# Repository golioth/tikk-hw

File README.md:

# Tikk Bluetooth Sensor / Output Board

We created the Tikk board as an affordable* board ($15 in low volume) for displaying the capabilities of Golioth's Bluetooth Connectivity. It plugs into a low cost ($3) Tenstar Robot nRF52840 breakout board, targeted at Keybord makers. We will have many of these nodes surrounding a Golioth gateway to showcase all of the uplink and downlink functions available to users. The focus was on easily demonstrated functions, such as LEDs and motor drivings for outputs and various in-tree Zephyr supported sensors for inputs.

## Rev A Preview Image

## Rev A Photos

## Features

This board has the following characteristics when soldered to something like the Tenstar Promicro

* 105 LEDs in 0402 format, individually addressable in a 7x15 matrix with the IS31FL3731
* Two H-Bridge chips (L9110S) for driving a single stepper or two dc motors
* 3 axis accelerometer (LIS2DH12)
* Temperature sensor (TMP102)
* QWIIC / Stemma header to expand breakout boards*
* User button
* Reset button
* A voltage divider that monitors battery voltage

Additional capabilities added by the Tenstar ProMicro and nRF52840

* Additional GPIOs I can solder to (5 digital, one analog)
* LiPo battery charger on board
* Load switch for all peripherals except motor driver
* USB Input to the nRF52840 (get serial terminal using USB-CDC)
* NFC tag emulation (via the nRF52840 and onboard flex connector)

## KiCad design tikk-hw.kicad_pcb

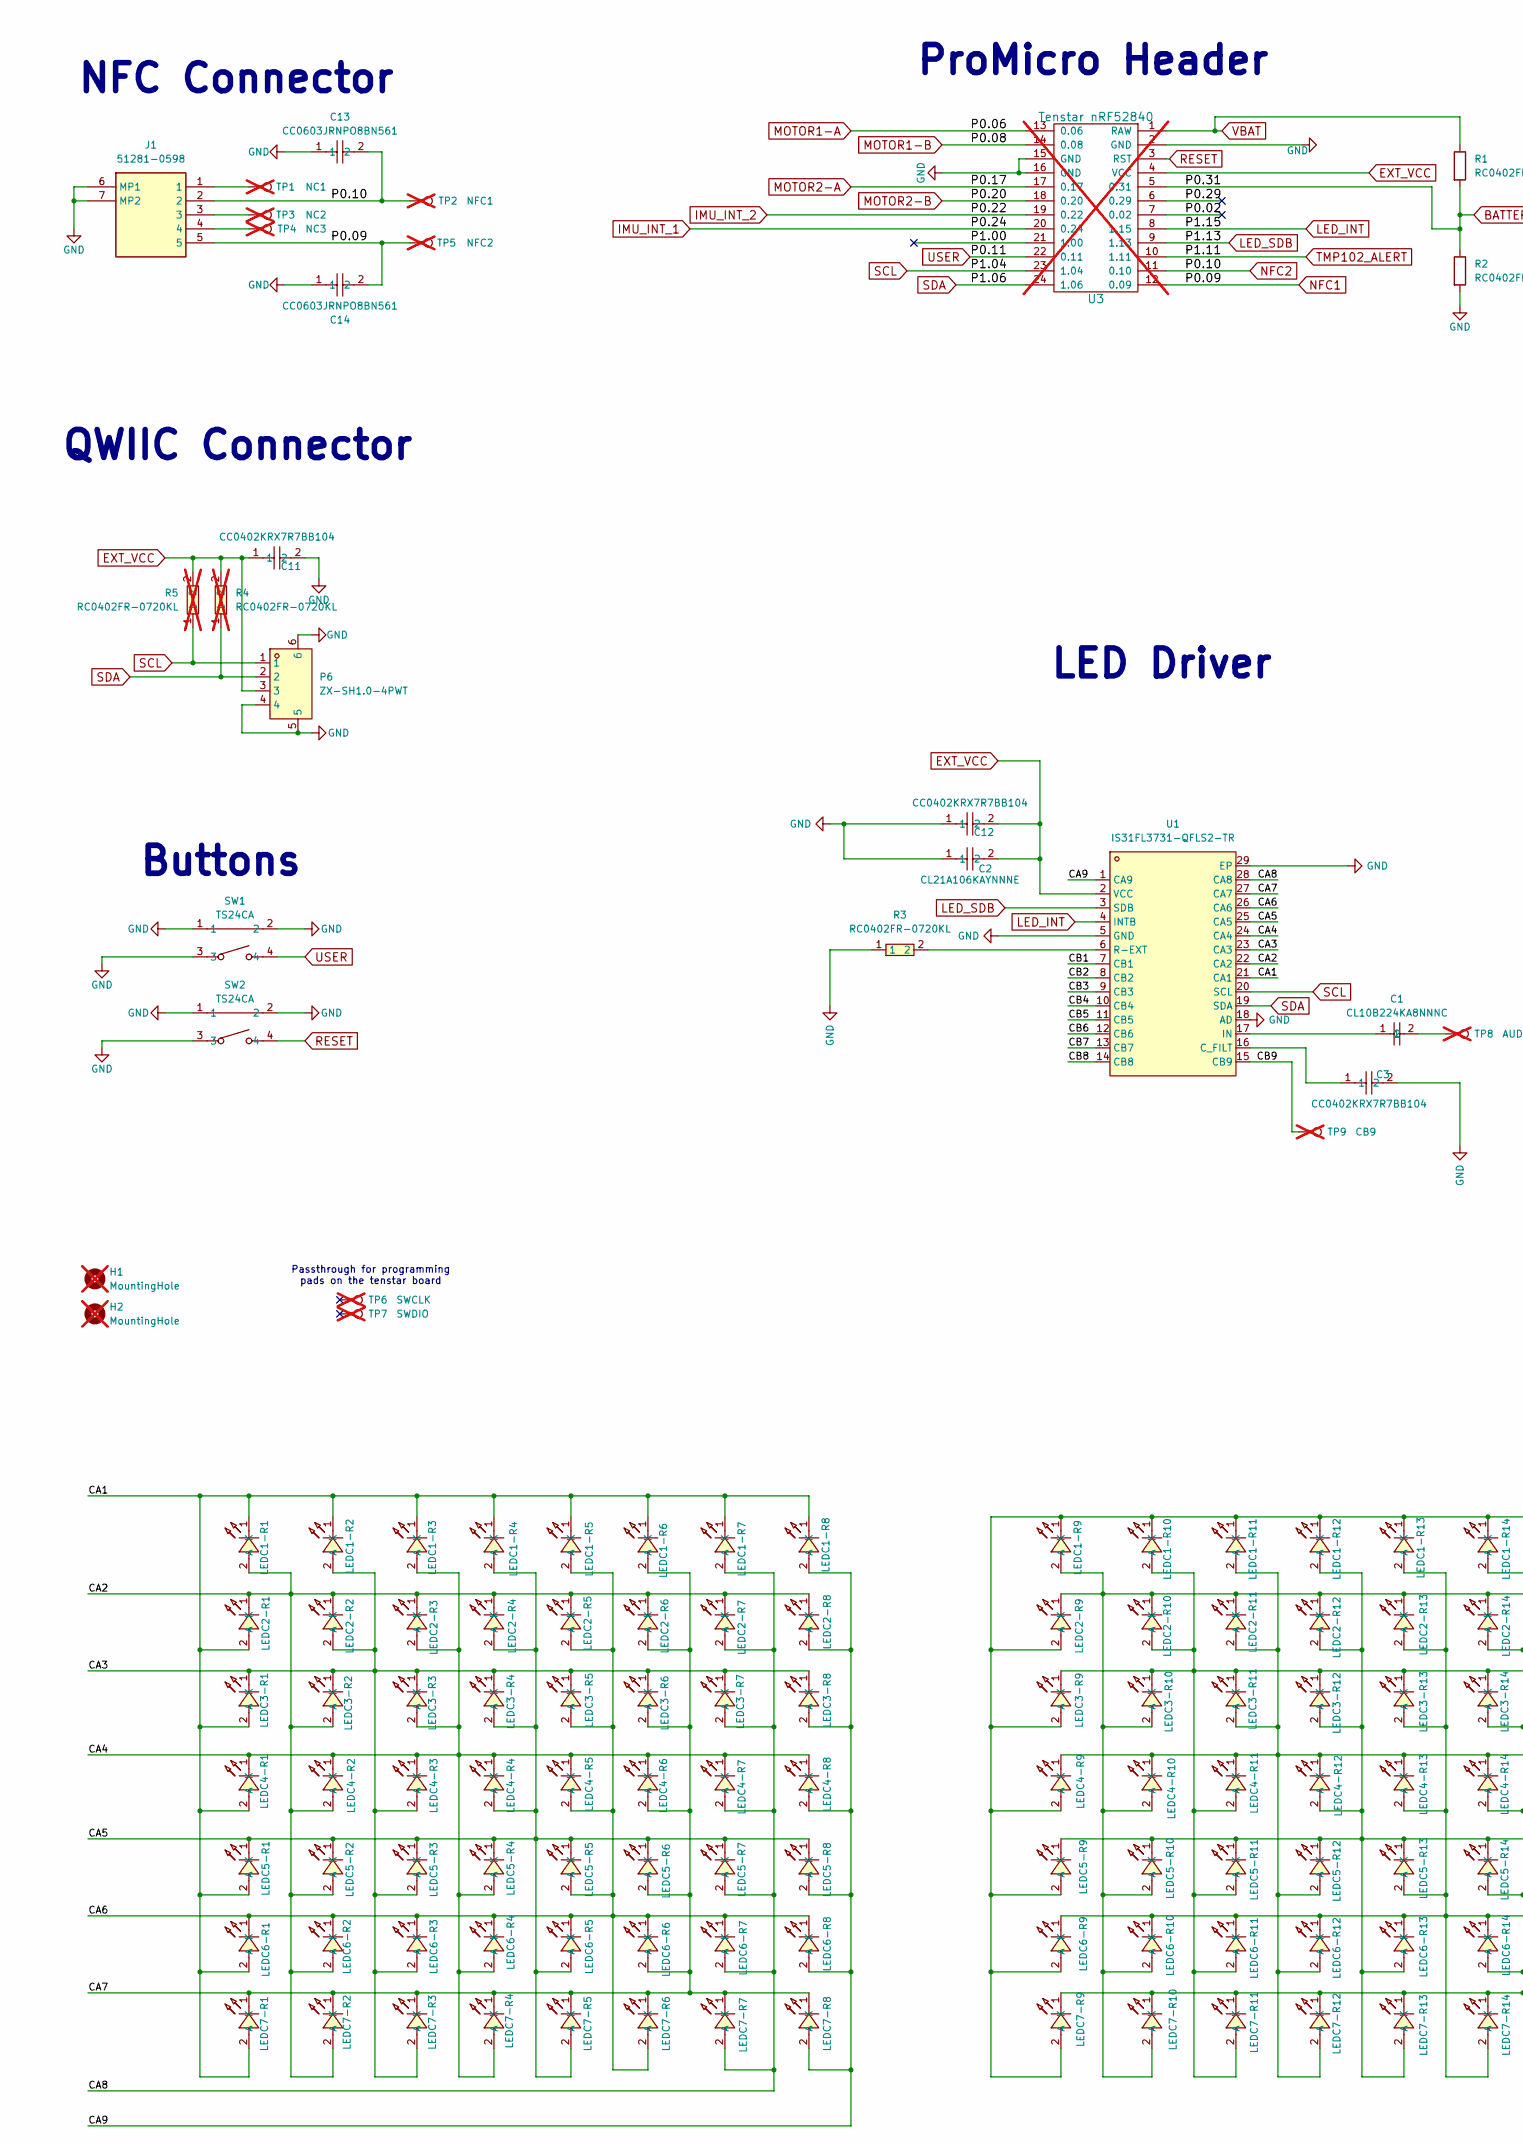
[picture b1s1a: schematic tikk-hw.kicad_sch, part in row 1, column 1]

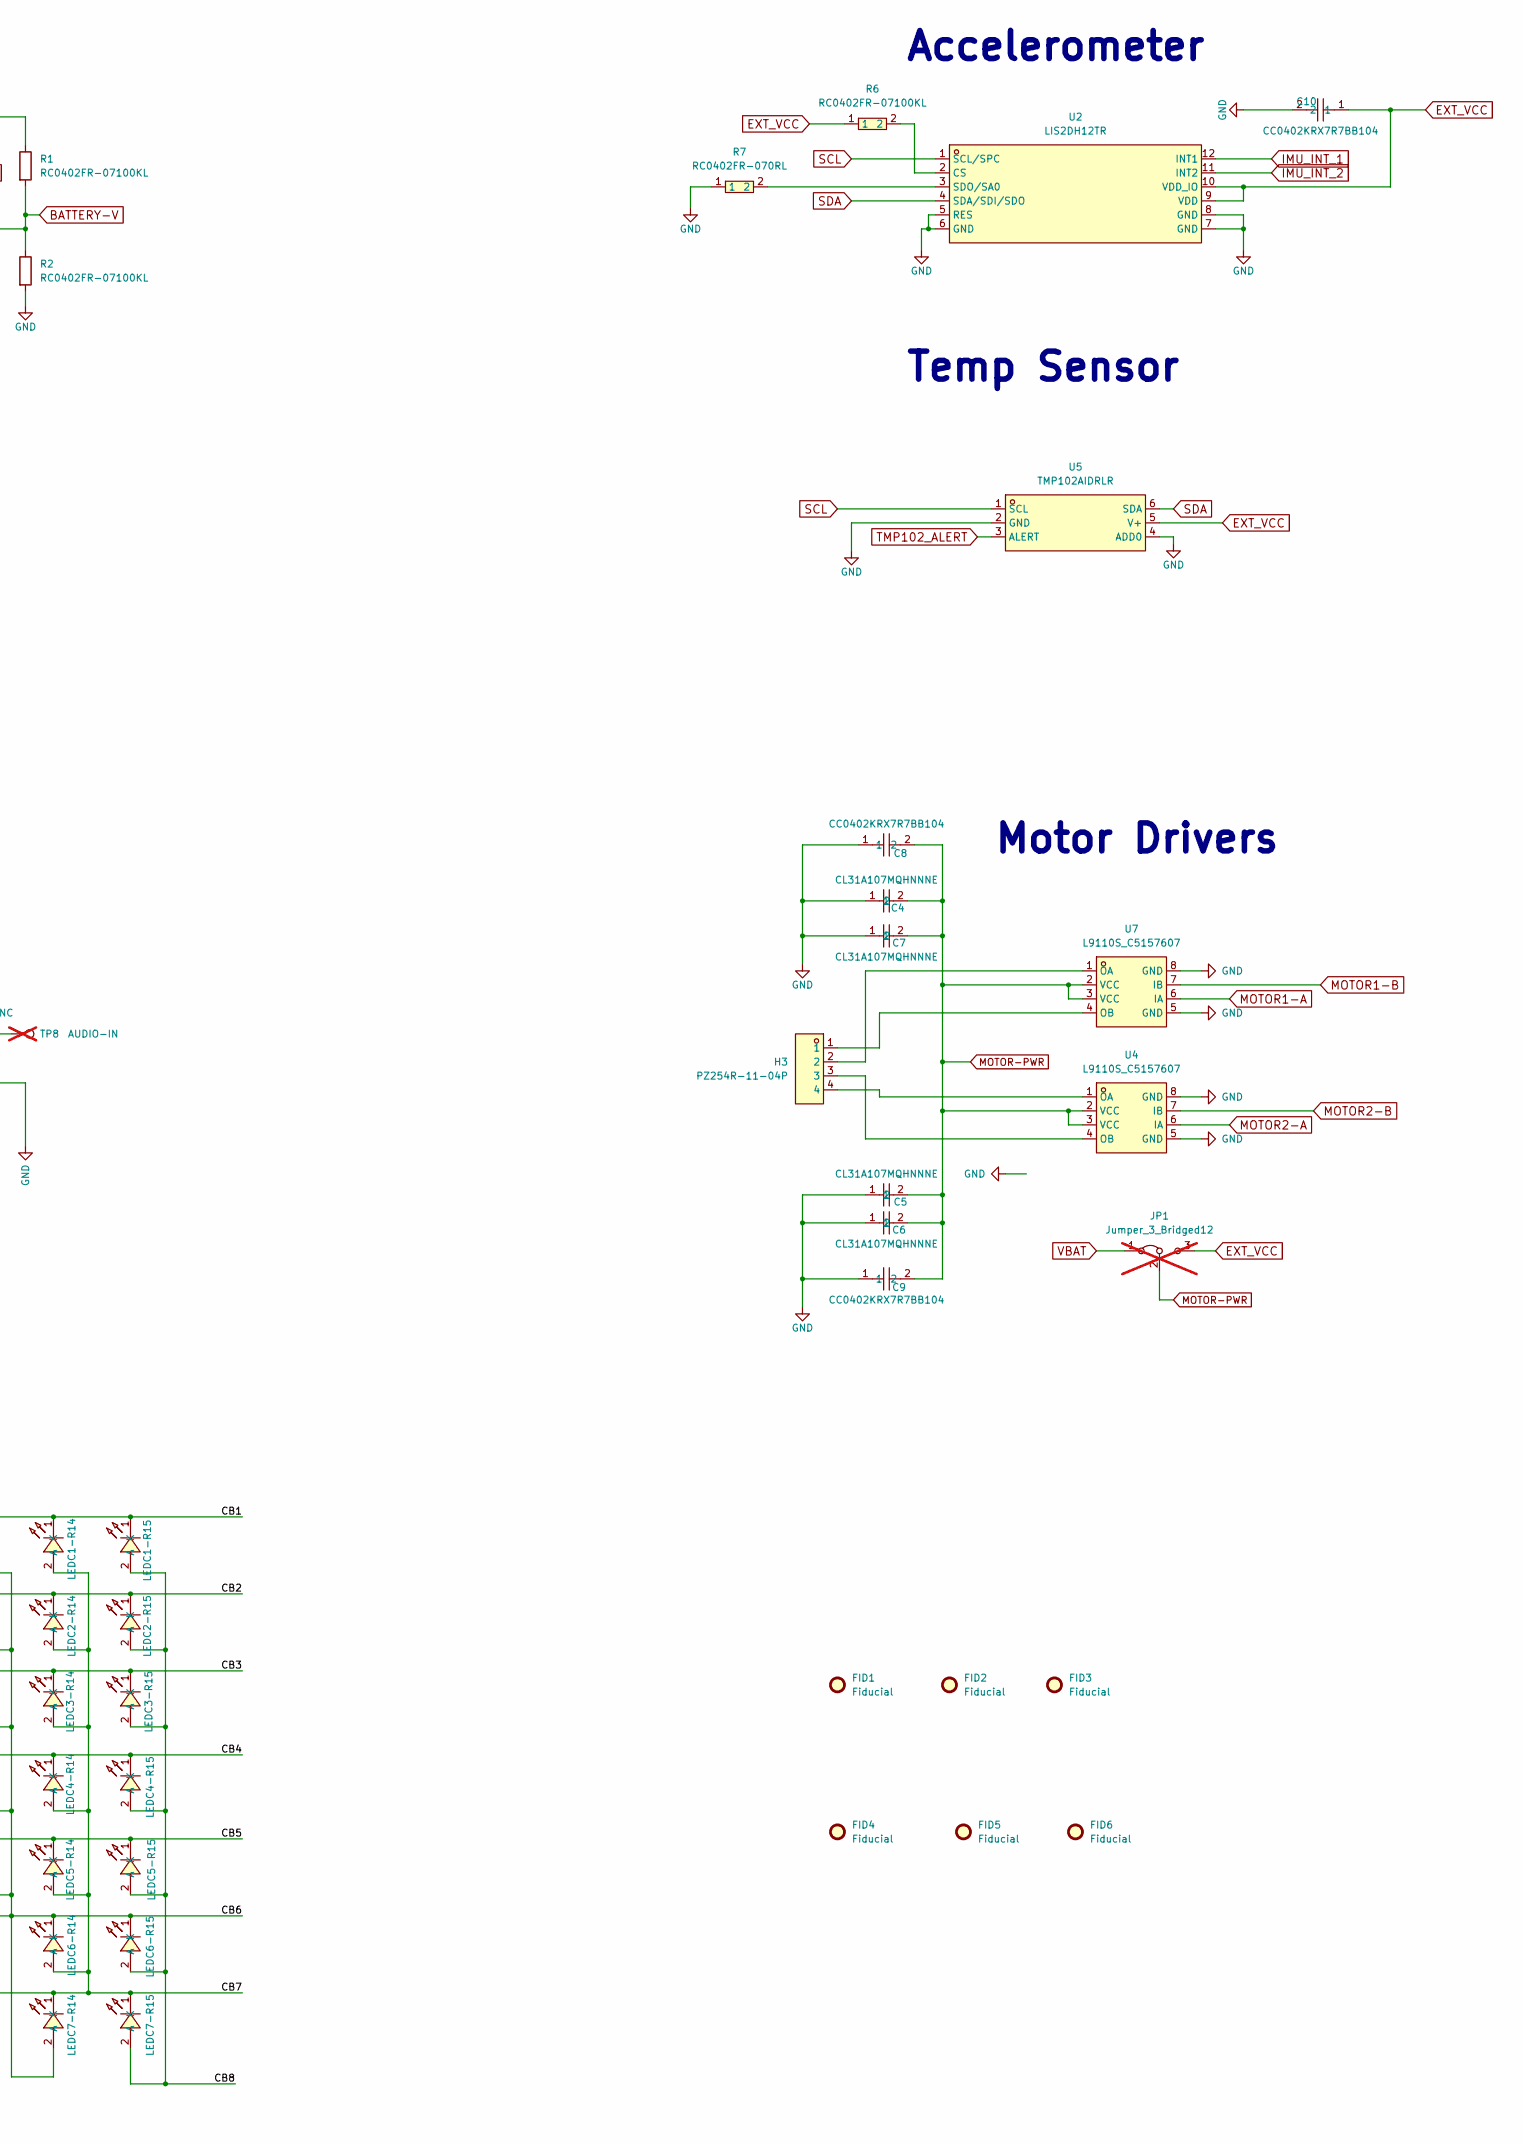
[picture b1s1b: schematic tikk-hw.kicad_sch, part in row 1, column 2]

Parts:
C1: CL10B224KA8NNNC; C0603; LCSC Part C21120
C2: CL21A106KAYNNNE; C0805; LCSC Part C15850
C3, C8, C9, C10, C11, C12: CC0402KRX7R7BB104; C0402; LCSC Part C60474
C4, C5, C6, C7: CL31A107MQHNNNE; C1206; LCSC Part C15008
C13, C14: CC0603JRNPO8BN561; C0603; LCSC Part C519396
FID1, FID2, FID3, FID4, FID5, FID6: Fiducial; Fiducial_0.5mm_Mask1mm
H1, H2: MountingHole; MountingHole_2.1mm; not fitted
H3: PZ254R-11-04P; HDR-TH_4P-P2.54-H-M-W10.4; LCSC Part C492412
J1: 51281-0598; 512810598; Mouser Part Number 538-51281-0598
JP1: Jumper_3_Bridged12; SolderJumper-3_P1.3mm_Bridged12_Pad1.0x1.5mm_NumberLabels; not fitted
LEDC1-R1, LEDC1-R2, LEDC1-R3, LEDC1-R4, LEDC1-R5, LEDC1-R6, LEDC1-R7, LEDC1-R8, LEDC1-R9, LEDC1-R10, LEDC1-R11, LEDC1-R12, LEDC1-R13, LEDC1-R14, LEDC1-R15, LEDC2-R1, LEDC2-R2, LEDC2-R3, LEDC2-R4, LEDC2-R5, LEDC2-R6, LEDC2-R7, LEDC2-R8, LEDC2-R9, LEDC2-R10, LEDC2-R11, LEDC2-R12, LEDC2-R13, LEDC2-R14, LEDC2-R15, LEDC3-R1, LEDC3-R2, LEDC3-R3, LEDC3-R4, LEDC3-R5, LEDC3-R6, LEDC3-R7, LEDC3-R8, LEDC3-R9, LEDC3-R10, LEDC3-R11, LEDC3-R12, LEDC3-R13, LEDC3-R14, LEDC3-R15, LEDC4-R1, LEDC4-R2, LEDC4-R3, LEDC4-R4, LEDC4-R5, LEDC4-R6, LEDC4-R7, LEDC4-R8, LEDC4-R9, LEDC4-R10, LEDC4-R11, LEDC4-R12, LEDC4-R13, LEDC4-R14, LEDC4-R15, LEDC5-R1, LEDC5-R2, LEDC5-R3, LEDC5-R4, LEDC5-R5, LEDC5-R6, LEDC5-R7, LEDC5-R8, LEDC5-R9, LEDC5-R10, LEDC5-R11, LEDC5-R12, LEDC5-R13, LEDC5-R14, LEDC5-R15, LEDC6-R1, LEDC6-R2, LEDC6-R3, LEDC6-R4, LEDC6-R5, LEDC6-R6, LEDC6-R7, LEDC6-R8, LEDC6-R9, LEDC6-R10, LEDC6-R11, LEDC6-R12, LEDC6-R13, LEDC6-R14, LEDC6-R15, LEDC7-R1, LEDC7-R2, LEDC7-R3, LEDC7-R4, LEDC7-R5, LEDC7-R6, LEDC7-R7, LEDC7-R8, LEDC7-R9, LEDC7-R10, LEDC7-R11, LEDC7-R12, LEDC7-R13, LEDC7-R14, LEDC7-R15: F.0402.00003/P2-0402R1TS2-045T-001; LED0402-RD; LCSC Part C7496803
P6: ZX-SH1.0-4PWT; CONN-SMD_4P-P1.00_MEGASTAR_ZX-SH1.0-4PWT; LCSC Part C7430446
R1, R2: RC0402FR-07100KL; R_0402_1005Metric
R3: RC0402FR-0720KL; R0402; LCSC Part C93942
R4, R5: RC0402FR-0720KL; R0402; LCSC Part C93942; not fitted
R6: RC0402FR-07100KL; R0402; LCSC Part C60491
R7: RC0402FR-070RL; R0402; LCSC Part C106231
SW1, SW2: TS24CA; SW-SMD_TS24CA; LCSC Part C393942
TP1: NC1; TestPoint_Pad_1.0x1.0mm; not fitted
TP2: NFC1; TestPoint_Pad_1.0x1.0mm; not fitted
TP3: NC2; TestPoint_Pad_1.0x1.0mm; not fitted
TP4: NC3; TestPoint_Pad_1.0x1.0mm; not fitted
TP5: NFC2; TestPoint_Pad_1.0x1.0mm; not fitted
TP6: SWCLK; TestPoint_THTPad_1.0x1.0mm_Drill0.5mm; not fitted
TP7: SWDIO; TestPoint_THTPad_1.0x1.0mm_Drill0.5mm; not fitted
TP8: AUDIO-IN; TestPoint_Pad_D1.0mm; not fitted
TP9: CB9; TestPoint_Pad_D1.0mm; not fitted
U1: IS31FL3731-QFLS2-TR; QFN-28_L4.0-W4.0-P0.40-BL-EP; LCSC Part C191206
U2: LIS2DH12TR; LGA-12_L2.0-W2.0-P0.50-BL; LCSC Part C110926
U3: Tenstar nRF52840; tenstar_nrf52840; not fitted
U4, U7: L9110S_C5157607; SOP-8_L4.9-W3.9-P1.27-LS6.0-BL; LCSC Part C5157607
U5: TMP102AIDRLR; SOT-563_L1.6-W1.2-P0.50-LS1.6-BR; LCSC Part C99269

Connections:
/CA1: LEDC1-R1.1 (K), LEDC1-R2.1 (K), LEDC1-R3.1 (K), LEDC1-R4.1 (K), LEDC1-R5.1 (K), LEDC1-R6.1 (K), LEDC1-R7.1 (K), LEDC1-R8.1 (K), LEDC2-R1.2 (A), LEDC3-R1.2 (A), LEDC4-R1.2 (A), LEDC5-R1.2 (A), LEDC6-R1.2 (A), LEDC7-R1.2 (A), U1.21 (CA1)
/CA2: LEDC1-R1.2 (A), LEDC2-R1.1 (K), LEDC2-R2.1 (K), LEDC2-R3.1 (K), LEDC2-R4.1 (K), LEDC2-R5.1 (K), LEDC2-R6.1 (K), LEDC2-R7.1 (K), LEDC2-R8.1 (K), LEDC3-R2.2 (A), LEDC4-R2.2 (A), LEDC5-R2.2 (A), LEDC6-R2.2 (A), LEDC7-R2.2 (A), U1.22 (CA2)
/CA3: LEDC1-R2.2 (A), LEDC2-R2.2 (A), LEDC3-R1.1 (K), LEDC3-R2.1 (K), LEDC3-R3.1 (K), LEDC3-R4.1 (K), LEDC3-R5.1 (K), LEDC3-R6.1 (K), LEDC3-R7.1 (K), LEDC3-R8.1 (K), LEDC4-R3.2 (A), LEDC5-R3.2 (A), LEDC6-R3.2 (A), LEDC7-R3.2 (A), U1.23 (CA3)
/CA4: LEDC1-R3.2 (A), LEDC2-R3.2 (A), LEDC3-R3.2 (A), LEDC4-R1.1 (K), LEDC4-R2.1 (K), LEDC4-R3.1 (K), LEDC4-R4.1 (K), LEDC4-R5.1 (K), LEDC4-R6.1 (K), LEDC4-R7.1 (K), LEDC4-R8.1 (K), LEDC5-R4.2 (A), LEDC6-R4.2 (A), LEDC7-R4.2 (A), U1.24 (CA4)
/CA5: LEDC1-R4.2 (A), LEDC2-R4.2 (A), LEDC3-R4.2 (A), LEDC4-R4.2 (A), LEDC5-R1.1 (K), LEDC5-R2.1 (K), LEDC5-R3.1 (K), LEDC5-R4.1 (K), LEDC5-R5.1 (K), LEDC5-R6.1 (K), LEDC5-R7.1 (K), LEDC5-R8.1 (K), LEDC6-R5.2 (A), LEDC7-R5.2 (A), U1.25 (CA5)
/CA6: LEDC1-R5.2 (A), LEDC2-R5.2 (A), LEDC3-R5.2 (A), LEDC4-R5.2 (A), LEDC5-R5.2 (A), LEDC6-R1.1 (K), LEDC6-R2.1 (K), LEDC6-R3.1 (K), LEDC6-R4.1 (K), LEDC6-R5.1 (K), LEDC6-R6.1 (K), LEDC6-R7.1 (K), LEDC6-R8.1 (K), LEDC7-R6.2 (A), U1.26 (CA6)
/CA7: LEDC1-R6.2 (A), LEDC2-R6.2 (A), LEDC3-R6.2 (A), LEDC4-R6.2 (A), LEDC5-R6.2 (A), LEDC6-R6.2 (A), LEDC7-R1.1 (K), LEDC7-R2.1 (K), LEDC7-R3.1 (K), LEDC7-R4.1 (K), LEDC7-R5.1 (K), LEDC7-R6.1 (K), LEDC7-R7.1 (K), LEDC7-R8.1 (K), U1.27 (CA7)
/CA8: LEDC1-R7.2 (A), LEDC2-R7.2 (A), LEDC3-R7.2 (A), LEDC4-R7.2 (A), LEDC5-R7.2 (A), LEDC6-R7.2 (A), LEDC7-R7.2 (A), U1.28 (CA8)
/CA9: LEDC1-R8.2 (A), LEDC2-R8.2 (A), LEDC3-R8.2 (A), LEDC4-R8.2 (A), LEDC5-R8.2 (A), LEDC6-R8.2 (A), LEDC7-R8.2 (A), U1.1 (CA9)
/CB1: LEDC1-R9.1 (K), LEDC1-R10.1 (K), LEDC1-R11.1 (K), LEDC1-R12.1 (K), LEDC1-R13.1 (K), LEDC1-R14.1 (K), LEDC1-R15.1 (K), LEDC2-R9.2 (A), LEDC3-R9.2 (A), LEDC4-R9.2 (A), LEDC5-R9.2 (A), LEDC6-R9.2 (A), LEDC7-R9.2 (A), U1.7 (CB1)
/CB2: LEDC1-R9.2 (A), LEDC2-R9.1 (K), LEDC2-R10.1 (K), LEDC2-R11.1 (K), LEDC2-R12.1 (K), LEDC2-R13.1 (K), LEDC2-R14.1 (K), LEDC2-R15.1 (K), LEDC3-R10.2 (A), LEDC4-R10.2 (A), LEDC5-R10.2 (A), LEDC6-R10.2 (A), LEDC7-R10.2 (A), U1.8 (CB2)
/CB3: LEDC1-R10.2 (A), LEDC2-R10.2 (A), LEDC3-R9.1 (K), LEDC3-R10.1 (K), LEDC3-R11.1 (K), LEDC3-R12.1 (K), LEDC3-R13.1 (K), LEDC3-R14.1 (K), LEDC3-R15.1 (K), LEDC4-R11.2 (A), LEDC5-R11.2 (A), LEDC6-R11.2 (A), LEDC7-R11.2 (A), U1.9 (CB3)
/CB4: LEDC1-R11.2 (A), LEDC2-R11.2 (A), LEDC3-R11.2 (A), LEDC4-R9.1 (K), LEDC4-R10.1 (K), LEDC4-R11.1 (K), LEDC4-R12.1 (K), LEDC4-R13.1 (K), LEDC4-R14.1 (K), LEDC4-R15.1 (K), LEDC5-R12.2 (A), LEDC6-R12.2 (A), LEDC7-R12.2 (A), U1.10 (CB4)
/CB5: LEDC1-R12.2 (A), LEDC2-R12.2 (A), LEDC3-R12.2 (A), LEDC4-R12.2 (A), LEDC5-R9.1 (K), LEDC5-R10.1 (K), LEDC5-R11.1 (K), LEDC5-R12.1 (K), LEDC5-R13.1 (K), LEDC5-R14.1 (K), LEDC5-R15.1 (K), LEDC6-R13.2 (A), LEDC7-R13.2 (A), U1.11 (CB5)
/CB6: LEDC1-R13.2 (A), LEDC2-R13.2 (A), LEDC3-R13.2 (A), LEDC4-R13.2 (A), LEDC5-R13.2 (A), LEDC6-R9.1 (K), LEDC6-R10.1 (K), LEDC6-R11.1 (K), LEDC6-R12.1 (K), LEDC6-R13.1 (K), LEDC6-R14.1 (K), LEDC6-R15.1 (K), LEDC7-R14.2 (A), U1.12 (CB6)
/CB7: LEDC1-R14.2 (A), LEDC2-R14.2 (A), LEDC3-R14.2 (A), LEDC4-R14.2 (A), LEDC5-R14.2 (A), LEDC6-R14.2 (A), LEDC7-R9.1 (K), LEDC7-R10.1 (K), LEDC7-R11.1 (K), LEDC7-R12.1 (K), LEDC7-R13.1 (K), LEDC7-R14.1 (K), LEDC7-R15.1 (K), U1.13 (CB7)
/CB8: LEDC1-R15.2 (A), LEDC2-R15.2 (A), LEDC3-R15.2 (A), LEDC4-R15.2 (A), LEDC5-R15.2 (A), LEDC6-R15.2 (A), LEDC7-R15.2 (A), U1.14 (CB8)
/CB9: TP9.1, U1.15 (CB9)
/P0.02: U3.7 (0.02)
/P0.29: U3.6 (0.29)
/P1.00: U3.21 (1.00)
BATTERY-V: R1.2, R2.1, U3.5 (0.31)
EXT_VCC: C2.2, C10.1, C11.1, C12.2, JP1.3 (B), P6.3, R4.2, R5.2, R6.1, U1.2 (VCC), U2.9 (VDD), U2.10 (VDD_IO), U3.4 (VCC), U5.5 (V+)
GND: C2.1, C3.2, C4.1, C5.1, C6.1, C7.1, C8.1, C9.1, C10.2, C11.2, C12.1, C13.1, C14.1, J1.6 (MP1), J1.7 (MP2), P6.4, P6.5, P6.6, R2.2, R3.1, R7.1, SW1.1, SW1.2, SW1.3, SW2.1, SW2.2, SW2.3, U1.5 (GND), U1.18 (AD), U1.29 (EP), U2.5 (RES), U2.6 (GND), U2.7 (GND), U2.8 (GND), U3.2 (GND), U3.15 (GND), U3.16 (GND), U4.5 (GND), U4.8 (GND), U5.2 (GND), U5.4 (ADD0), U7.5 (GND), U7.8 (GND)
IMU_INT_1: U2.12 (INT1), U3.20 (0.24)
IMU_INT_2: U2.11 (INT2), U3.19 (0.22)
LED_INT: U1.4 (INTB), U3.8 (1.15)
LED_SDB: U1.3 (SDB), U3.9 (1.13)
MOTOR1-A: U3.13 (0.06), U7.6 (IA)
MOTOR1-B: U3.14 (0.08), U7.7 (IB)
MOTOR2-A: U3.17 (0.17), U4.6 (IA)
MOTOR2-B: U3.18 (0.20), U4.7 (IB)
MOTOR-PWR: C4.2, C5.2, C6.2, C7.2, C8.2, C9.2, JP1.2 (C), U4.2 (VCC), U4.3 (VCC), U7.2 (VCC), U7.3 (VCC)
NFC1: C14.2, J1.5, TP5.1, U3.12 (0.09)
NFC2: C13.2, J1.2, TP2.1, U3.11 (0.10)
unnamed: C1.2, TP8.1
unnamed: J1.1, TP1.1
unnamed: J1.3, TP3.1
unnamed: J1.4, TP4.1
unnamed: C3.1, U1.16 (C_FILT)
unnamed: C1.1, U1.17 (IN)
unnamed: R3.2, U1.6 (R-EXT)
unnamed: R6.2, U2.2 (CS)
unnamed: R7.2, U2.3 (SDO/SA0)
unnamed: H3.4, U4.1 (OA)
unnamed: H3.3, U4.4 (OB)
unnamed: H3.2, U7.1 (OA)
unnamed: H3.1, U7.4 (OB)
RESET: SW2.4, U3.3 (RST)
SCL: P6.1, R5.1, U1.20 (SCL), U2.1 (SCL/SPC), U3.23 (1.04), U5.1 (SCL)
SDA: P6.2, R4.1, U1.19 (SDA), U2.4 (SDA/SDI/SDO), U3.24 (1.06), U5.6 (SDA)
TMP102_ALERT: U3.10 (1.11), U5.3 (ALERT)
USER: SW1.4, U3.22 (0.11)
VBAT: JP1.1 (A), R1.1, U3.1 (RAW)

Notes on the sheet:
Accelerometer
NFC Connector
Temp Sensor
LED Driver
Passthrough for programming pads on the tenstar board
Motor Drivers
Buttons
QWIIC Connector
ProMicro Header

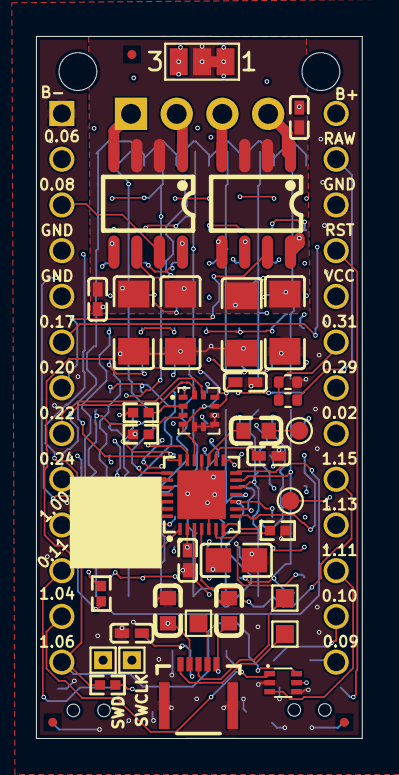
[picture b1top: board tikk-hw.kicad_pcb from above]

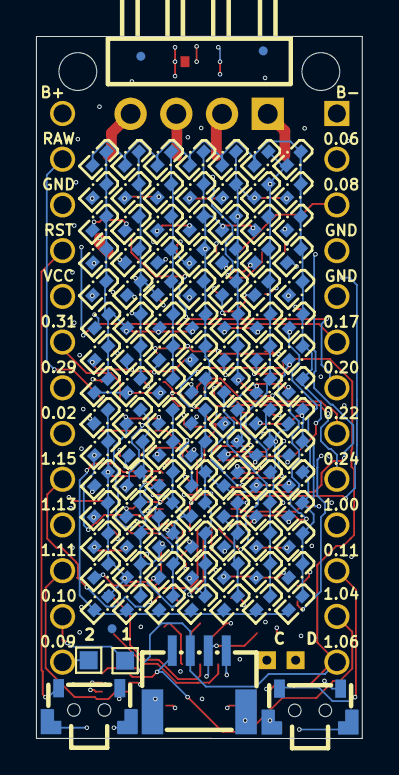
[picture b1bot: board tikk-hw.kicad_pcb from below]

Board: 4 copper layers, 18.1 x 39.0 mm, 155 parts (116 on the bottom side), 51 nets.

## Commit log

2025-07-08 project setup with gitignore and submodule
2025-07-08 update gitignore to forego autosave and jlc files
2025-07-08 initial board concept
2025-07-11 initial placements all finished
2025-07-12 added caps
2025-07-16 midway through routing LED matrix
2025-07-16 all connections to LEDs made on schematics
2025-07-17 finished initial layout
2025-07-18 Removed all initial DRC violations
2025-07-18 updated to add silkscreen qr code area and optimized component info
2025-07-18 add fiducials for mfg
2025-07-22 final changes before sending to JLC
2025-07-28 fix node assignment for user button (listed as 0.13, actually is 0.11)
2025-07-28 Add readme
2025-07-28 Update README.md
    Added Rev A images
2025-08-21 Update README.md with images/description
2025-08-21 Add license and CoC
2025-08-21 Clean up repo before open sourcing, pull in final data changes on schematic
